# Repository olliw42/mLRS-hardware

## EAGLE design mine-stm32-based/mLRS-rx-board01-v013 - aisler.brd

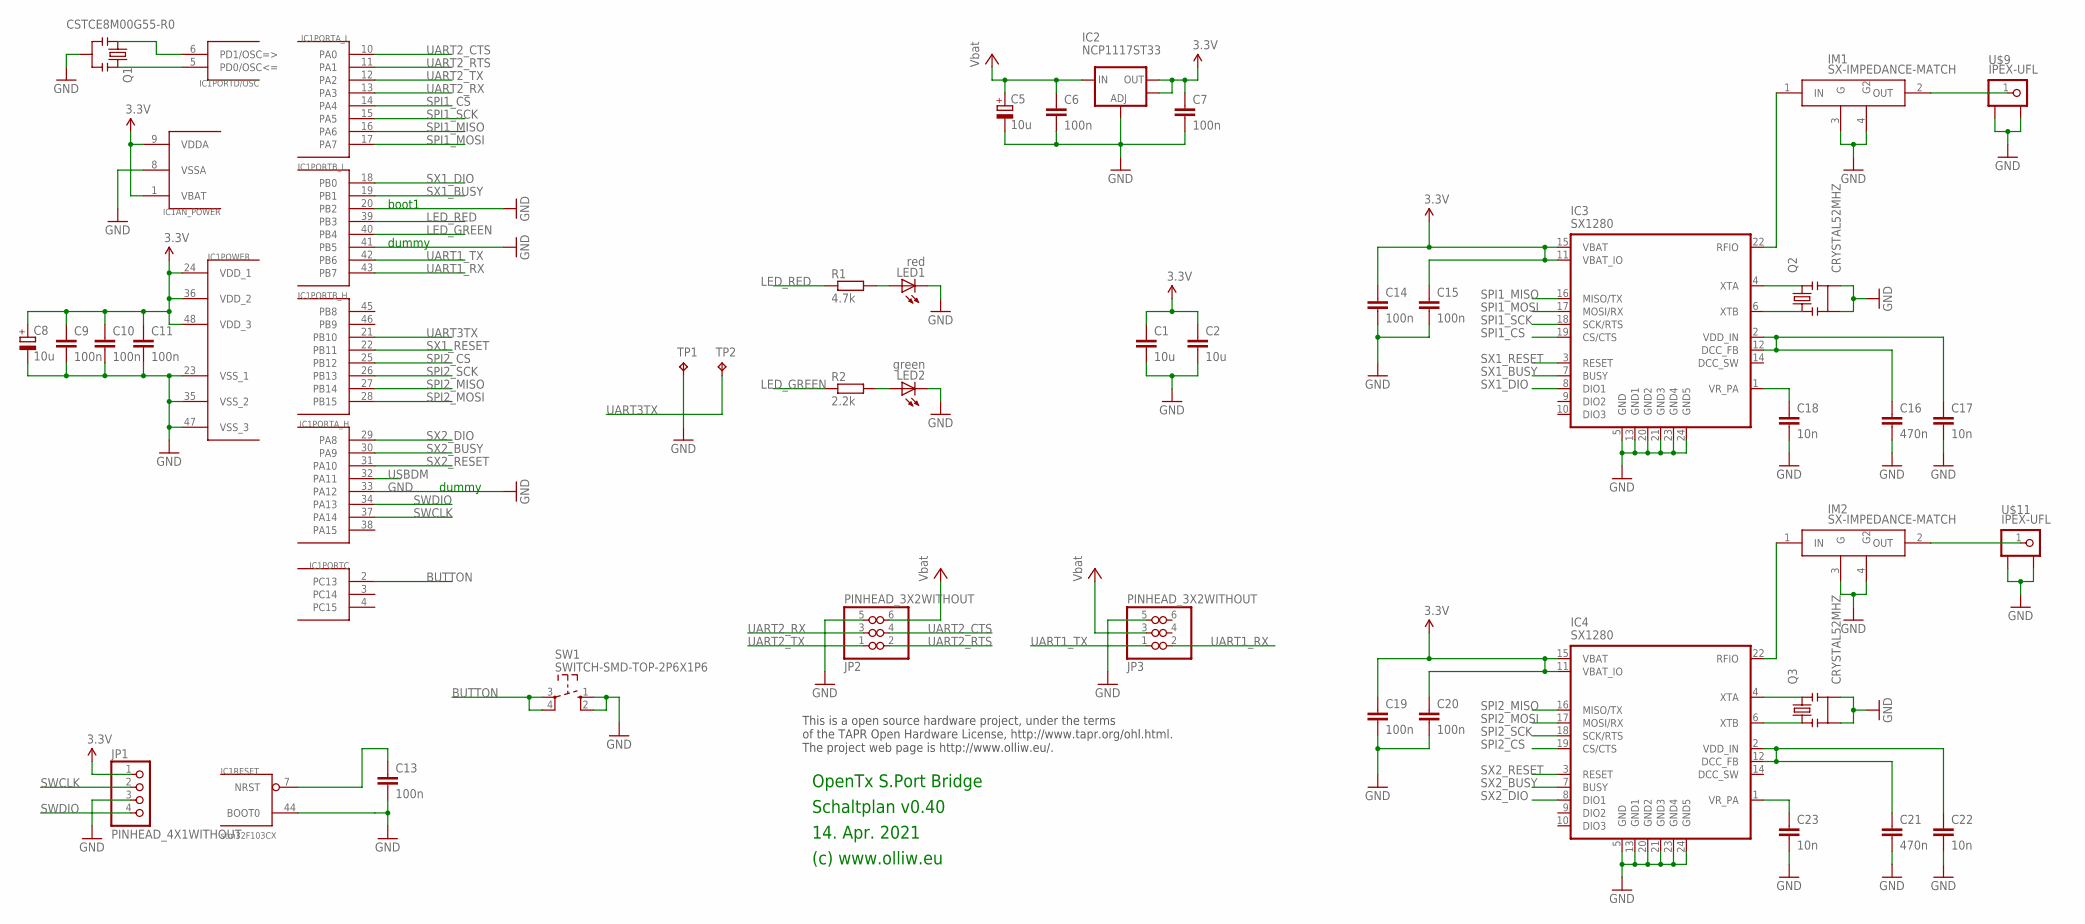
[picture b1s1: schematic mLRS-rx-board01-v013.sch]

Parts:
C1, C2: 10u; C0603
C5, C8: 10u; SMC_A
C6, C7, C9, C10, C11, C13: 100n; C0603
C14, C15, C19, C20: 100n; C0402
C16, C21: 470n; C0402
C17, C18, C22, C23: 10n; C0402
IC1: stm32F103CX; TQFP48
IC2: NCP1117ST33; SOT223
IC3, IC4: SX1280; QFN24-4X4-SX128X
IM1, IM2: SX-IMPEDANCE-MATCH
JP1: PINHEAD_4X1WITHOUT; PINHEAD_4X1_WO
JP2, JP3: PINHEAD_3X2WITHOUT; PINHEAD_3X2_WO
LED1: red; CHIPLED_0603
LED2: green; CHIPLED_0603
Q1: CSTCE8M00G55-R0; RESONATOR-SMD
Q2, Q3: CRYSTAL52MHZ; CRYSTAL-SMD-2X1P6-GND
R1: 4.7k; R0402
R2: 2.2k; R0402
SW1: SWITCH-SMD-TOP-2P6X1P6; TACTILE-SWITCH-SMD-TOP-2P6X1X6
TP1, TP2: TPB1,27; B1,27
U$9, U$11: IPEX-UFL; IPEX-UFL-SMD

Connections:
3.3V: C1.1, C2.1, C7.1, C8.+, C9.1, C10.1, C11.1, C14.1, C15.1, C19.1, C20.1, IC1.1 (VBAT), IC1.9 (VDDA), IC1.24 (VDD_1), IC1.36 (VDD_2), IC1.48 (VDD_3), IC2.2 (OUT), IC2.4 (OUT), IC3.11 (VBAT_IO), IC3.15 (VBAT), IC4.11 (VBAT_IO), IC4.15 (VBAT), JP1.1
BUTTON: IC1.2 (PC13), SW1.3, SW1.4
GND: C1.2, C2.2, C5.-, C6.2, C7.2, C8.-, C9.2, C10.2, C11.2, C13.2, C14.2, C15.2, C16.2, C17.2, C18.2, C19.2, C20.2, C21.2, C22.2, C23.2, IC1.8 (VSSA), IC1.20 (PB2), IC1.23 (VSS_1), IC1.33 (PA12), IC1.35 (VSS_2), IC1.41 (PB5), IC1.44 (BOOT0), IC1.47 (VSS_3), IC2.1 (ADJ), IC3.5 (GND), IC3.13 (GND1), IC3.20 (GND2), IC3.21 (GND3), IC3.23 (GND4), IC3.24 (GND5), IC4.5 (GND), IC4.13 (GND1), IC4.20 (GND2), IC4.21 (GND3), IC4.23 (GND4), IC4.24 (GND5), IM1.3 (G), IM1.4 (G2), IM2.3 (G), IM2.4 (G2), JP1.3, JP2.5, JP3.5, LED1.C, LED2.C, Q1.2, Q2.2, Q2.4, Q3.2, Q3.4, SW1.1, SW1.2, TP1.TP, U$9.2, U$9.3, U$11.2, U$11.3
LED_GREEN: IC1.40 (PB4), R2.1
LED_RED: IC1.39 (PB3), R1.1
unnamed: IC4.4 (XTA), Q3.3
unnamed: C21.1, C22.1, IC4.2 (VDD_IN), IC4.12 (DCC_FB)
unnamed: C23.1, IC4.1 (VR_PA)
unnamed: IC4.6 (XTB), Q3.1
unnamed: C13.1, IC1.7 (NRST)
unnamed: IC4.22 (RFIO), IM2.1 (IN)
unnamed: C16.1, C17.1, IC3.2 (VDD_IN), IC3.12 (DCC_FB)
unnamed: C18.1, IC3.1 (VR_PA)
unnamed: IC3.4 (XTA), Q2.3
unnamed: IC1.5 (PD0/OSC<=), Q1.3
unnamed: IC3.6 (XTB), Q2.1
unnamed: IC1.6 (PD1/OSC=>), Q1.1
unnamed: IC3.22 (RFIO), IM1.1 (IN)
unnamed: IM1.2 (OUT), U$9.1
unnamed: LED1.A, R1.2
unnamed: IM2.2 (OUT), U$11.1
unnamed: LED2.A, R2.2
SPI1_CS: IC1.14 (PA4), IC3.19 (CS/CTS)
SPI1_MISO: IC1.16 (PA6), IC3.16 (MISO/TX)
SPI1_MOSI: IC1.17 (PA7), IC3.17 (MOSI/RX)
SPI1_SCK: IC1.15 (PA5), IC3.18 (SCK/RTS)
SPI2_CS: IC1.25 (PB12), IC4.19 (CS/CTS)
SPI2_MISO: IC1.27 (PB14), IC4.16 (MISO/TX)
SPI2_MOSI: IC1.28 (PB15), IC4.17 (MOSI/RX)
SPI2_SCK: IC1.26 (PB13), IC4.18 (SCK/RTS)
SWCLK: IC1.37 (PA14), JP1.2
SWDIO: IC1.34 (PA13), JP1.4
SX1_BUSY: IC1.19 (PB1), IC3.7 (BUSY)
SX1_DIO: IC1.18 (PB0), IC3.8 (DIO1)
SX1_RESET: IC1.22 (PB11), IC3.3 (RESET)
SX2_BUSY: IC1.30 (PA9), IC4.7 (BUSY)
SX2_DIO: IC1.29 (PA8), IC4.8 (DIO1)
SX2_RESET: IC1.31 (PA10), IC4.3 (RESET)
UART1_RX: IC1.43 (PB7), JP3.2
UART1_TX: IC1.42 (PB6), JP3.1
UART2_CTS: IC1.10 (PA0), JP2.4
UART2_RTS: IC1.11 (PA1), JP2.2
UART2_RX: IC1.13 (PA3), JP2.3
UART2_TX: IC1.12 (PA2), JP2.1
UART3TX: IC1.21 (PB10), TP2.TP
USBDM: IC1.32 (PA11)
VCC: C5.+, C6.1, IC2.3 (IN), JP2.6, JP3.3

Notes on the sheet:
14. Apr. 2021
(c) www.olliw.eu
OpenTx S.Port Bridge
Schaltplan v0.40
This is a open source hardware project, under the terms of the TAPR Open Hardware License, http://www.tapr.org/ohl.html. The project web page is http://www.olliw.eu/.
boot1
dummy

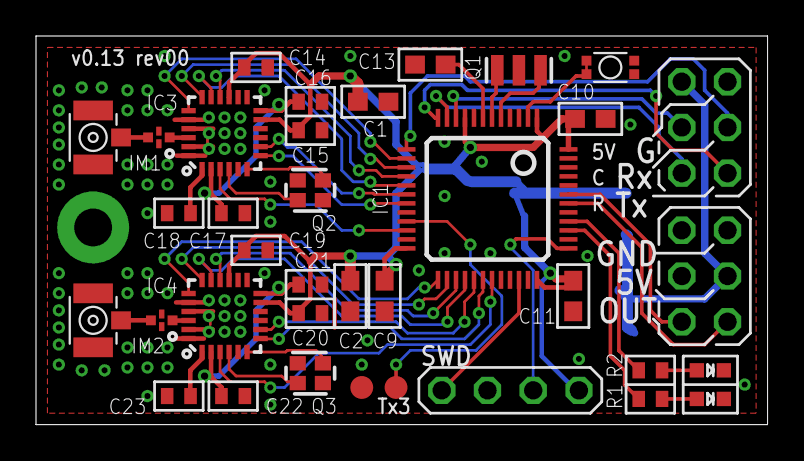
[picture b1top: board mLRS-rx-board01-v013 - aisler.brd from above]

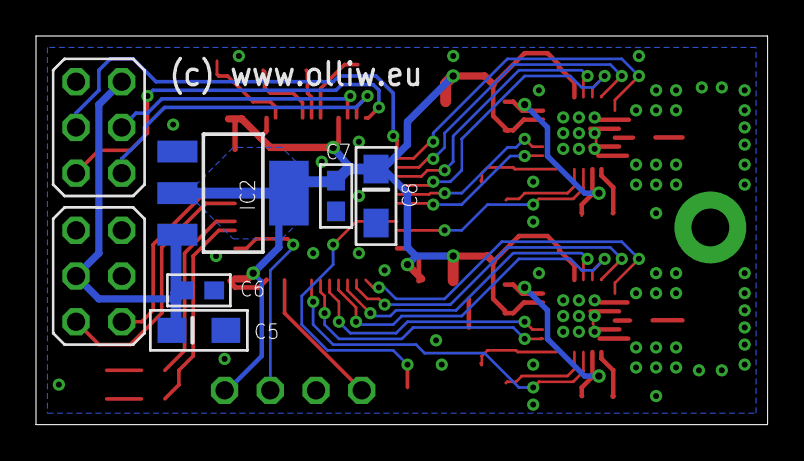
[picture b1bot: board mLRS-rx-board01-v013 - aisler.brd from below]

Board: 2 copper layers, 40.6 x 21.6 mm, 41 parts (5 on the bottom side), 46 nets.

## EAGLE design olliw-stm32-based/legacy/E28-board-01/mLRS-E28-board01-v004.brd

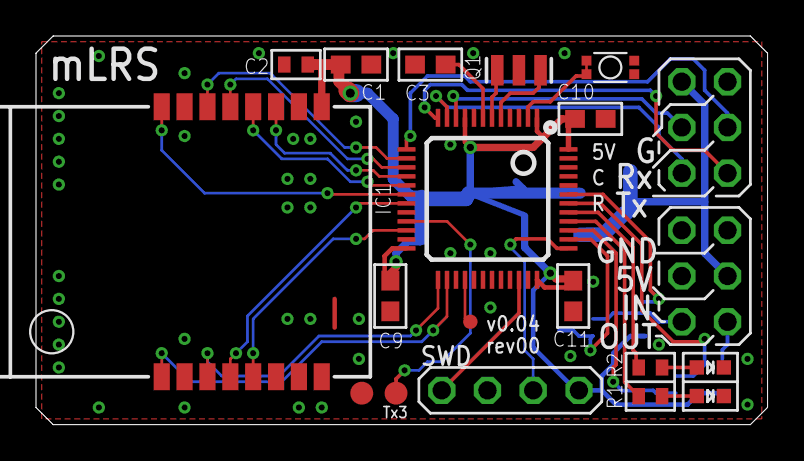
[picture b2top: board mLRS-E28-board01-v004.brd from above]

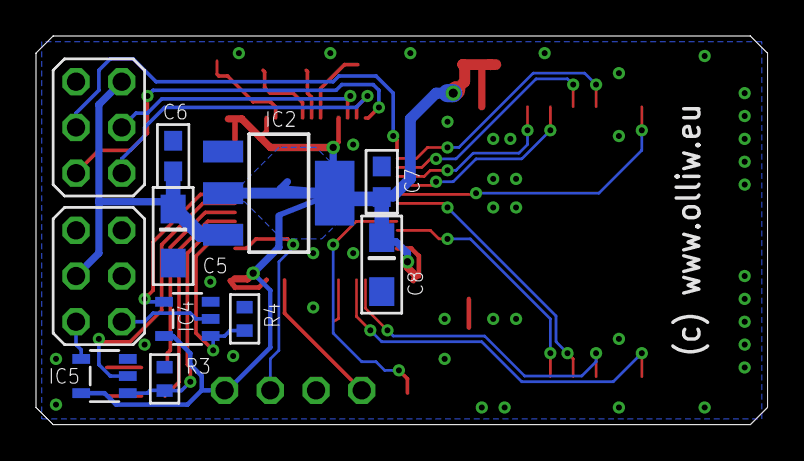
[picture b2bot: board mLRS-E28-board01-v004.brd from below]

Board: 2 copper layers, 40.6 x 21.6 mm, 29 parts (9 on the bottom side), 34 nets.

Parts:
C1: 10u; C0603
C2: 100n; C0402
C3, C6, C7, C9, C10, C11: 100n; C0603
C5, C8: 10u; SMC_A
IC1: STM32F103CB; TQFP48
IC2: NCP1117ST33; SOT223
IC3: E28-2G4M27S; E28-2G4M27
IC4, IC5: 74AHC1G86; SOT23-5-VER1
LED1: red; CHIPLED_0603
LED2: green; CHIPLED_0603
PH-OUT: PINHEAD_3X2WITHOUT; PINHEAD_3X2_WO
PH-SERIAL: PINHEAD_3X2WITHOUT; PINHEAD_3X2_WO
PH-SWD: PINHEAD_4X1WITHOUT; PINHEAD_4X1_WO
Q1: CSTCE8M00G55-R0; RESONATOR-SMD
R1: 4.7k; R0402
R2: 2.2k; R0402
R3, R4: 10k; R0402
S1: SWITCH-SMD-TOP-2P6X1P6; TACTILE-SWITCH-SMD-TOP-2P6X1X6
TP1, TP2: TPB1,27; B1,27
TP3: TPTP08R; TP08R

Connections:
3.3V: C1.1, C2.1, C7.1, C8.+, C9.1, C10.1, C11.1, IC1.1, IC1.9, IC1.24, IC1.36, IC1.48, IC2.2, IC2.4, IC3.1, IC4.5, IC5.5, PH-SWD.1
BUTTON: IC1.2, S1.3, S1.4
GND: C1.2, C2.2, C3.2, C5.-, C6.2, C7.2, C8.-, C9.2, C10.2, C11.2, IC1.3, IC1.4, IC1.8, IC1.20, IC1.23, IC1.27, IC1.29, IC1.33, IC1.35, IC1.44, IC1.47, IC2.1, IC3.2, IC3.7, IC3.10, IC3.16, IC4.3, IC5.3, LED1.C, LED2.C, PH-OUT.5, PH-SERIAL.5, PH-SWD.3, Q1.2, R3.1, R4.1, S1.1, S1.2, TP1.TP
IN: IC4.2, PH-OUT.2
LED_GREEN: IC1.41, R2.1
LED_RED: IC1.40, R1.1
unnamed: C3.1, IC1.7
unnamed: IC1.28, TP3.TP
unnamed: IC1.5, Q1.3
unnamed: IC1.6, Q1.1
unnamed: LED1.A, R1.2
unnamed: LED2.A, R2.2
OUT: IC5.4, PH-OUT.1
SPI1_CS: IC1.14, IC3.6
SPI1_MISO: IC1.16, IC3.3
SPI1_MOSI: IC1.17, IC3.4
SPI1_SCK: IC1.15, IC3.5
SWCLK: IC1.37, PH-SWD.2
SWDIO: IC1.34, PH-SWD.4
SX1_BUSY: IC1.19, IC3.12
SX1_DIO: IC1.22, IC3.13
SX1_RESET: IC1.25, IC3.11
SX1_RX_EN: IC1.18, IC3.8
SX1_TX_EN: IC1.26, IC3.9
UART1_RX: IC1.43, IC4.4
UART1_TX: IC1.42, IC5.2
UART2_CTS: IC1.10, PH-SERIAL.4
UART2_RTS: IC1.11, PH-SERIAL.2
UART2_RX: IC1.13, PH-SERIAL.3
UART2_TX: IC1.12, PH-SERIAL.1
UART3TX: IC1.21, TP2.TP
VCC: C5.+, C6.1, IC2.3, PH-OUT.3, PH-SERIAL.6
XOR: IC1.39, IC5.1, R3.2
XOR_RX: IC1.38, IC4.1, R4.2

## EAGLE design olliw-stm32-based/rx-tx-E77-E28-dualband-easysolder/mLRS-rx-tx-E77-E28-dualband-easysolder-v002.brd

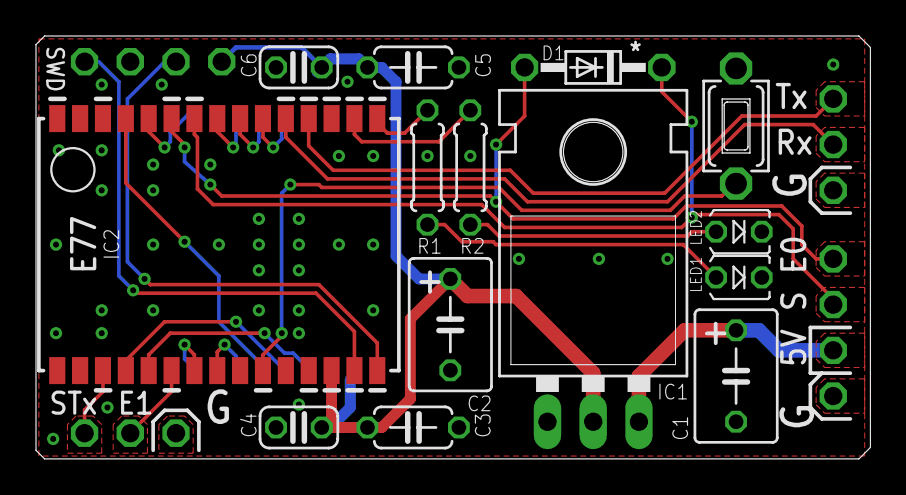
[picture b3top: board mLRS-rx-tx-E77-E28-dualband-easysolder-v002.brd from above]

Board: 2 copper layers, 46.4 x 23.5 mm, 19 parts (1 on the bottom side), 25 nets.

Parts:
C1, C2: 10u; C050-045X075
C3, C5: 10u; C050-024X044
C4, C6: 100n; C025-024X044
D1: BAT42; D_7.5
IC1: LD1117AV33; TO220L1
IC2: E77-900M22S
IC3: E28-SX; E28-2G4M27SX
LED1: red; LED1.8MM
LED2: green; LED1.8MM
PH1, PH3: PINHEAD_4X1WITHOUT; PINHEAD_4X1_WO
PH2, PH4: PINHEAD_3X1WITHOUT; PINHEAD_3X1_WO
R1, R2: 330; R0204/6.25
SW1: BUTTON6X3.5; BUTTON-THT

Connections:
3.3V: C2.1, C3.1, C4.1, C5.1, C6.1, IC1.2, IC2.28, IC3.1, PH1.1
BUTTON: IC2.25, SW1.1
GND: C1.2, C2.2, C3.2, C4.2, C5.2, C6.2, IC1.1, IC2.3, IC2.13, IC2.15, IC2.27, IC3.2, IC3.7, IC3.10, IC3.16, LED1.K, LED2.K, PH1.3, PH2.3, PH3.4, PH4.3, SW1.2
LED_GREEN: IC2.2, R2.1
LED_RED: IC2.1, R1.1
unnamed: LED1.A, R1.2
unnamed: LED2.A, R2.2
PIN_EXTRA1: IC2.21, PH4.2
SPI1_CS: IC2.23, IC3.6
SPI1_MISO: IC2.20, IC3.3
SPI1_MOSI: IC2.19, IC3.4
SPI1_SCK: IC2.12, IC3.5
SWCLK: IC2.30, PH1.2
SWDIO: IC2.29, PH1.4
SWUART_TX: IC2.18, PH4.1
SX2_BUSY: IC2.7, IC3.12
SX2_DIO: IC2.6, IC3.13
SX2_RESET: IC2.8, IC3.11
SX2_RX_EN: IC2.22, IC3.8
SX2_TX_EN: IC2.11, IC3.9
UART1_RX: IC2.5, PH2.2
UART1_TX: IC2.4, PH2.1
UART2_RX: D1.A, IC2.10, PH3.1
UART2_TX: D1.C, IC2.9, PH3.2
VCC: C1.1, IC1.3, PH3.3

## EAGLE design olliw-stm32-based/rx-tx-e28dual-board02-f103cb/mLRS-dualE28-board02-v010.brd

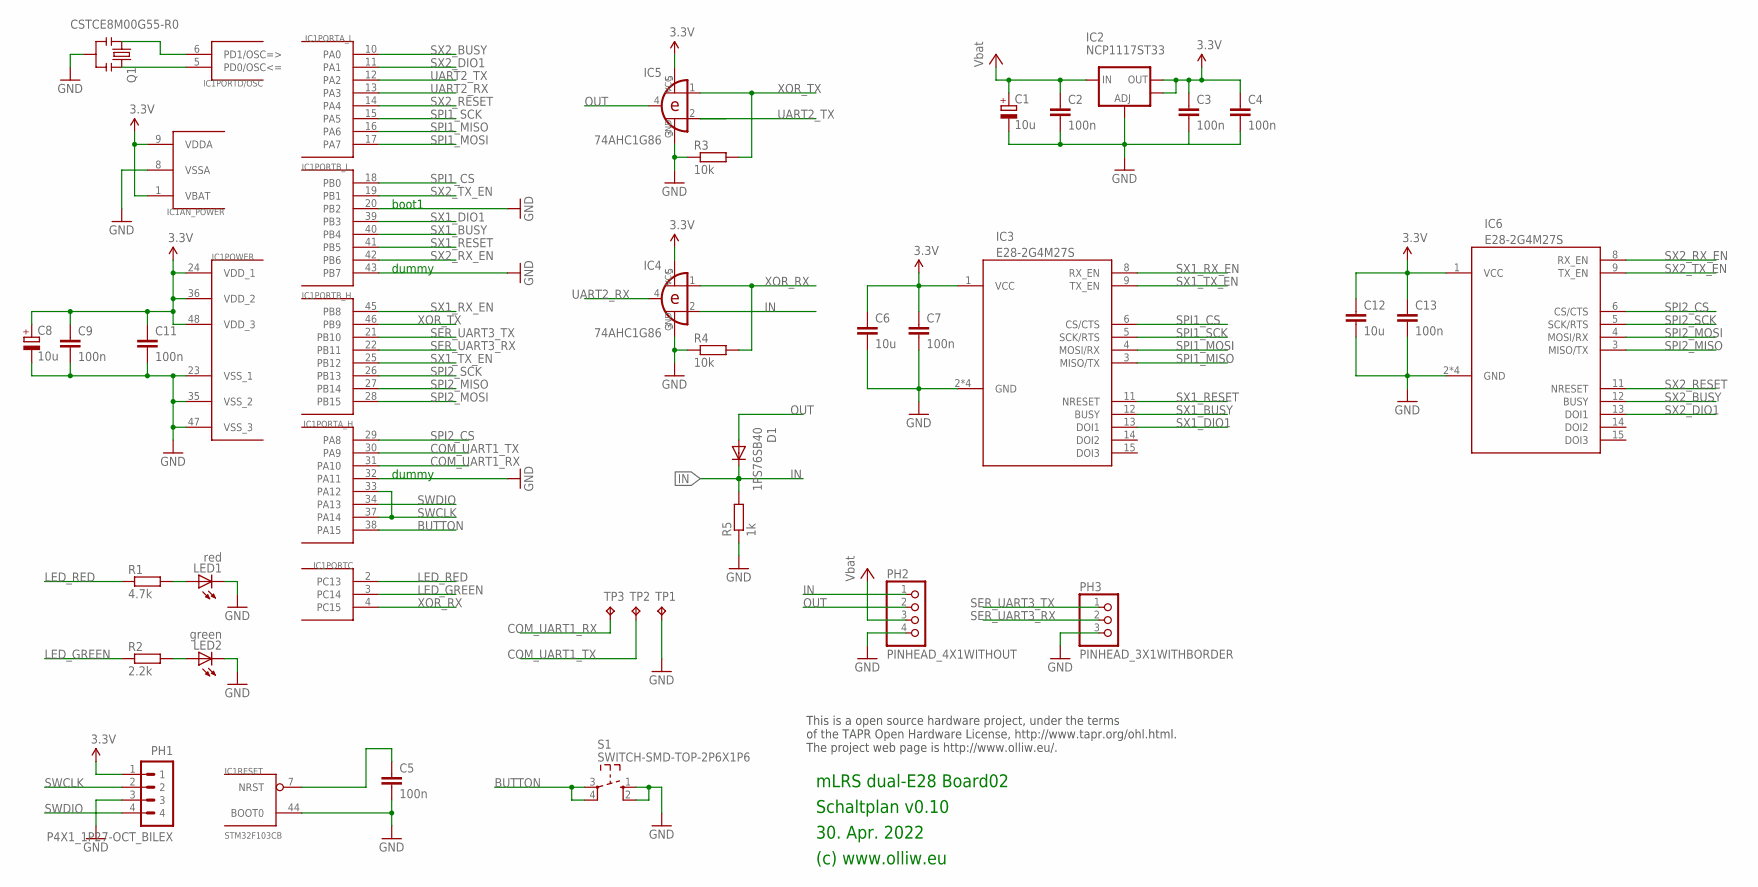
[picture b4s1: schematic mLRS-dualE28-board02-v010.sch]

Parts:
C1, C8: 10u; SMC_A
C2: 100n; C0603
C3, C4, C5, C7, C9, C11, C13: 100n; C0402
C6, C12: 10u; C0603
D1: 1PS76SB40; SOD110-R
IC1: STM32F103CB; TQFP48
IC2: NCP1117ST33; SOT223
IC3, IC6: E28-2G4M27S; E28-2G4M27
IC4, IC5: 74AHC1G86; SOT23-5-VER1
LED1: red; CHIPLED_0603
LED2: green; CHIPLED_0603
PH1: P4X1_1P27-OCT_BILEX; 4X1_1P27_OCT_BILEX
PH2: PINHEAD_4X1WITHOUT; PINHEAD_4X1_WO
PH3: PINHEAD_3X1WITHBORDER; PINHEAD_3X1
Q1: CSTCE8M00G55-R0; RESONATOR-SMD
R1: 4.7k; R0402
R2: 2.2k; R0402
R3, R4: 10k; R0402
R5: 1k; R0402
S1: SWITCH-SMD-TOP-2P6X1P6; TACTILE-SWITCH-SMD-TOP-2P6X1X6
TP1, TP2, TP3: TPB1,27; B1,27

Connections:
3.3V: C3.1, C4.1, C6.1, C7.1, C8.+, C9.1, C11.1, C12.1, C13.1, IC1.1 (VBAT), IC1.9 (VDDA), IC1.24 (VDD_1), IC1.36 (VDD_2), IC1.48 (VDD_3), IC2.2 (OUT), IC2.4 (OUT), IC3.1 (VCC), IC4.5 (VCC), IC5.5 (VCC), IC6.1 (VCC), PH1.1
BUTTON: IC1.38 (PA15), S1.3, S1.4
COM_UART1_RX: IC1.31 (PA10), TP3.TP
COM_UART1_TX: IC1.30 (PA9), TP2.TP
GND: C1.-, C2.2, C3.2, C4.2, C5.2, C6.2, C7.2, C8.-, C9.2, C11.2, C12.2, C13.2, IC1.8 (VSSA), IC1.20 (PB2), IC1.23 (VSS_1), IC1.32 (PA11), IC1.35 (VSS_2), IC1.43 (PB7), IC1.44 (BOOT0), IC1.47 (VSS_3), IC2.1 (ADJ), IC3.2 (GND), IC3.7 (GND), IC3.10 (GND), IC3.16 (GND), IC4.3 (GND), IC5.3 (GND), IC6.2 (GND), IC6.7 (GND), IC6.10 (GND), IC6.16 (GND), LED1.C, LED2.C, PH1.3, PH2.4, PH3.3 (5), Q1.2, R3.1, R4.1, R5.1, S1.1, S1.2, TP1.TP
IN: D1.C, IC4.2 (I1), PH2.1, R5.2
LED_GREEN: IC1.3 (PC14), R2.1
LED_RED: IC1.2 (PC13), R1.1
unnamed: C5.1, IC1.7 (NRST)
unnamed: IC1.5 (PD0/OSC<=), Q1.3
unnamed: IC1.6 (PD1/OSC=>), Q1.1
unnamed: LED1.A, R1.2
unnamed: LED2.A, R2.2
OUT: D1.A, IC5.4 (O), PH2.2
SER_UART3_RX: IC1.22 (PB11), PH3.2 (3)
SER_UART3_TX: IC1.21 (PB10), PH3.1
SPI1_CS: IC1.18 (PB0), IC3.6 (CS/CTS)
SPI1_MISO: IC1.16 (PA6), IC3.3 (MISO/TX)
SPI1_MOSI: IC1.17 (PA7), IC3.4 (MOSI/RX)
SPI1_SCK: IC1.15 (PA5), IC3.5 (SCK/RTS)
SPI2_CS: IC1.29 (PA8), IC6.6 (CS/CTS)
SPI2_MISO: IC1.27 (PB14), IC6.3 (MISO/TX)
SPI2_MOSI: IC1.28 (PB15), IC6.4 (MOSI/RX)
SPI2_SCK: IC1.26 (PB13), IC6.5 (SCK/RTS)
SWCLK: IC1.33 (PA12), IC1.37 (PA14), PH1.2
SWDIO: IC1.34 (PA13), PH1.4
SX1_BUSY: IC1.40 (PB4), IC3.12 (BUSY)
SX1_DIO1: IC1.39 (PB3), IC3.13 (DOI1)
SX1_RESET: IC1.41 (PB5), IC3.11 (NRESET)
SX1_RX_EN: IC1.45 (PB8), IC3.8 (RX_EN)
SX1_TX_EN: IC1.25 (PB12), IC3.9 (TX_EN)
SX2_BUSY: IC1.10 (PA0), IC6.12 (BUSY)
SX2_DIO1: IC1.11 (PA1), IC6.13 (DOI1)
SX2_RESET: IC1.14 (PA4), IC6.11 (NRESET)
SX2_RX_EN: IC1.42 (PB6), IC6.8 (RX_EN)
SX2_TX_EN: IC1.19 (PB1), IC6.9 (TX_EN)
UART2_RX: IC1.13 (PA3), IC4.4 (O)
UART2_TX: IC1.12 (PA2), IC5.2 (I1)
VCC: C1.+, C2.1, IC2.3 (IN), PH2.3
XOR_RX: IC1.4 (PC15), IC4.1 (I0), R4.2
XOR_TX: IC1.46 (PB9), IC5.1 (I0), R3.2

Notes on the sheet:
30. Apr. 2022
(c) www.olliw.eu
mLRS dual-E28 Board02
Schaltplan v0.10
This is a open source hardware project, under the terms of the TAPR Open Hardware License, http://www.tapr.org/ohl.html. The project web page is http://www.olliw.eu/.
boot1
dummy

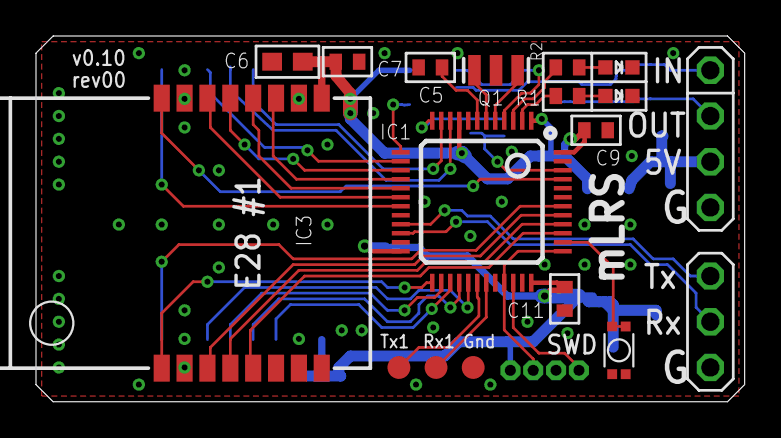
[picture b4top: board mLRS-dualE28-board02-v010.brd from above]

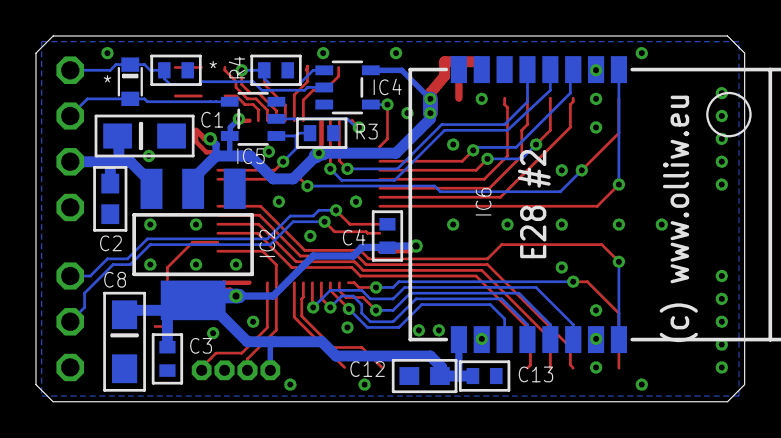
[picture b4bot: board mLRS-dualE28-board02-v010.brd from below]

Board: 2 copper layers, 39.4 x 20.3 mm, 34 parts (15 on the bottom side), 41 nets.

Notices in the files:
parts and their libraries:
Licensing: CC v3.0 Share-Alike You are welcome to use this library for commercial purposes.
